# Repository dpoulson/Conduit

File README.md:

Conduit
=======

Conduit LARP equipment

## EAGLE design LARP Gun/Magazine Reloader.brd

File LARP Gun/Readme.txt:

Magazine uses ATTiny45

3 Analog inputs
2 PWM inputs

Program for Magazine:

Pin 0 - High if still ammo left
Pin 1 - Trigger (decrement ammo count by one)
Pin 2 - Add ammo (Admin only)
Pin 3 - Clear ammo (Admin only)

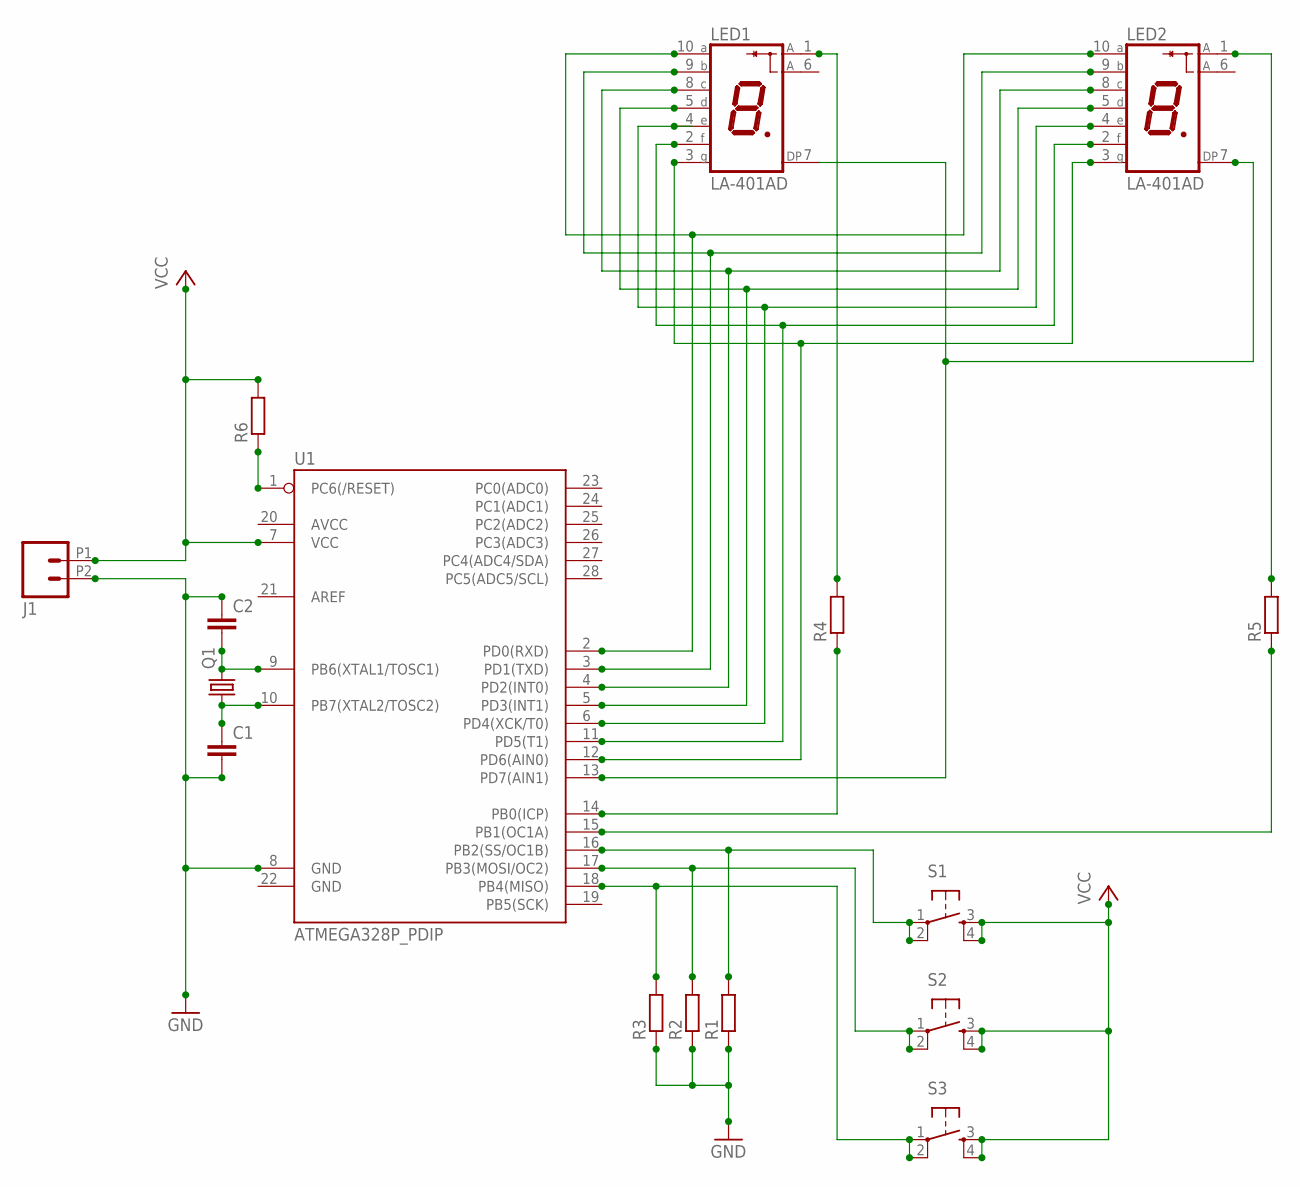
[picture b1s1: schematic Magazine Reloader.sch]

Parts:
C1, C2: C-EU025-025X050; C025-025X050
J1: M022.54MM_SCREWTERM; 1X02_2.54_SCREWTERM
LED1, LED2: LA-401AD; LA-401
Q1: CRYSTALHC49S; HC49/S
R1, R2, R3, R4, R5, R6: R-EU_0207/7; 0207/7
S1, S2, S3: TAC_SWITCHPTH; TACTILE-PTH
U1: ATMEGA328P_PDIP; DIL28-3

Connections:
GND: C1.2, C2.1, J1.P2 (2), R1.1, R2.1, R3.1, U1.8 (GND)
unnamed: LED1.3 (G), LED2.3 (G), U1.12 (PD6(AIN0))
unnamed: LED1.2 (F), LED2.2 (F), U1.11 (PD5(T1))
unnamed: LED1.4 (E), LED2.4 (E), U1.6 (PD4(XCK/T0))
unnamed: LED1.5 (D), LED2.5 (D), U1.5 (PD3(INT1))
unnamed: LED1.8 (C), LED2.8 (C), U1.4 (PD2(INT0))
unnamed: LED1.9 (B), LED2.9 (B), U1.3 (PD1(TXD))
unnamed: LED1.10 (A), LED2.10 (A), U1.2 (PD0(RXD))
unnamed: LED1.7 (DP), LED2.7 (DP), U1.13 (PD7(AIN1))
unnamed: R4.1, U1.14 (PB0(ICP))
unnamed: R5.1, U1.15 (PB1(OC1A))
unnamed: LED1.1 (A), R4.2
unnamed: LED2.1 (A), R5.2
unnamed: R3.2, S3.1, S3.2, U1.18 (PB4(MISO))
unnamed: R2.2, S2.1, S2.2, U1.17 (PB3(MOSI/OC2))
unnamed: R1.2, S1.1, S1.2, U1.16 (PB2(SS/OC1B))
unnamed: C2.2, Q1.2, U1.9 (PB6(XTAL1/TOSC1))
unnamed: C1.1, Q1.1, U1.10 (PB7(XTAL2/TOSC2))
unnamed: R6.1, U1.1 (PC6(/RESET))
VCC: J1.P1 (1), R6.2, S1.3, S1.4, S2.3, S2.4, S3.3, S3.4, U1.7 (VCC)

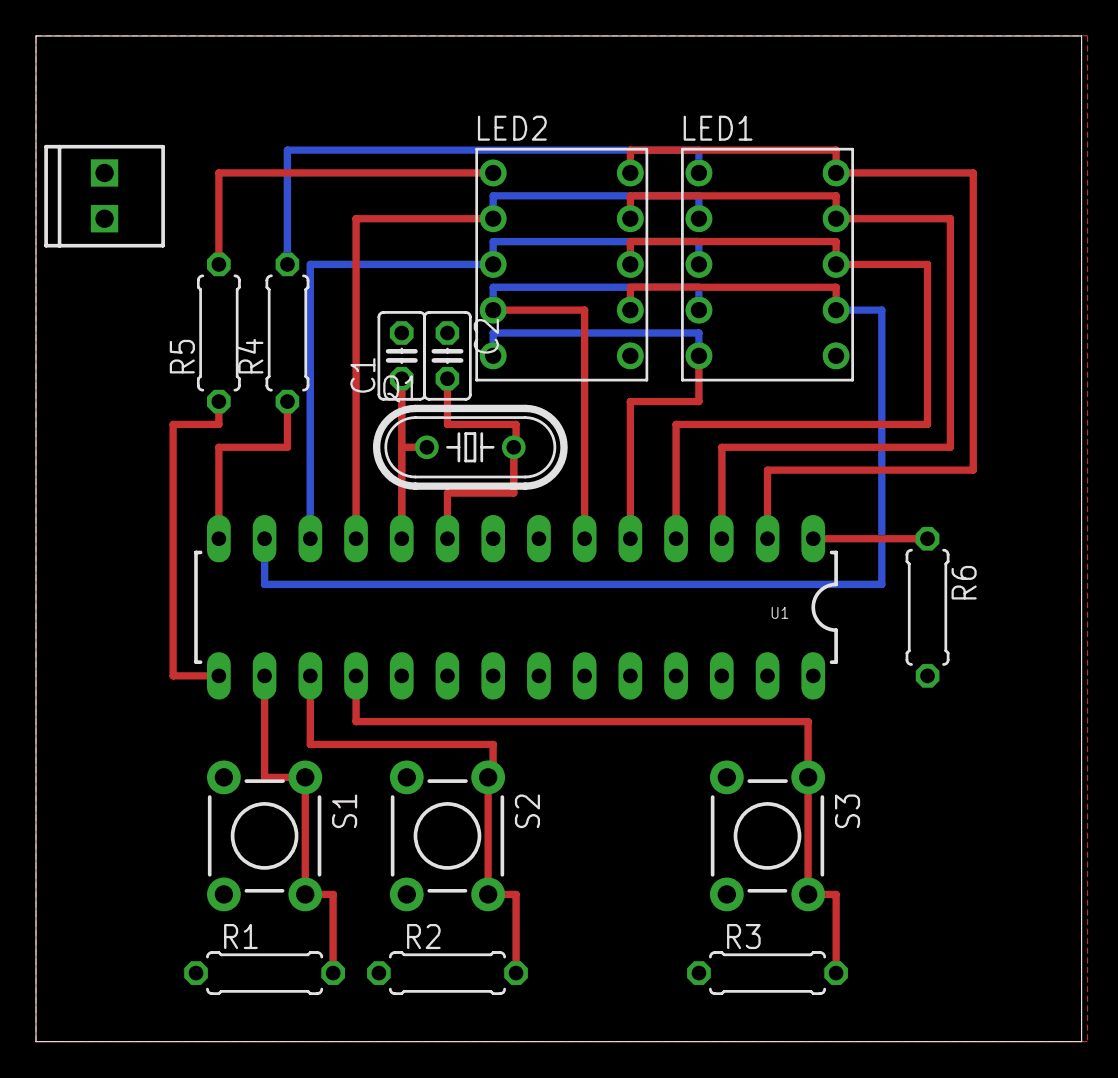
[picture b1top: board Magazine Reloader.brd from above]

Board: 2 copper layers, 58.1 x 55.9 mm, 16 parts (0 on the bottom side), 20 nets.

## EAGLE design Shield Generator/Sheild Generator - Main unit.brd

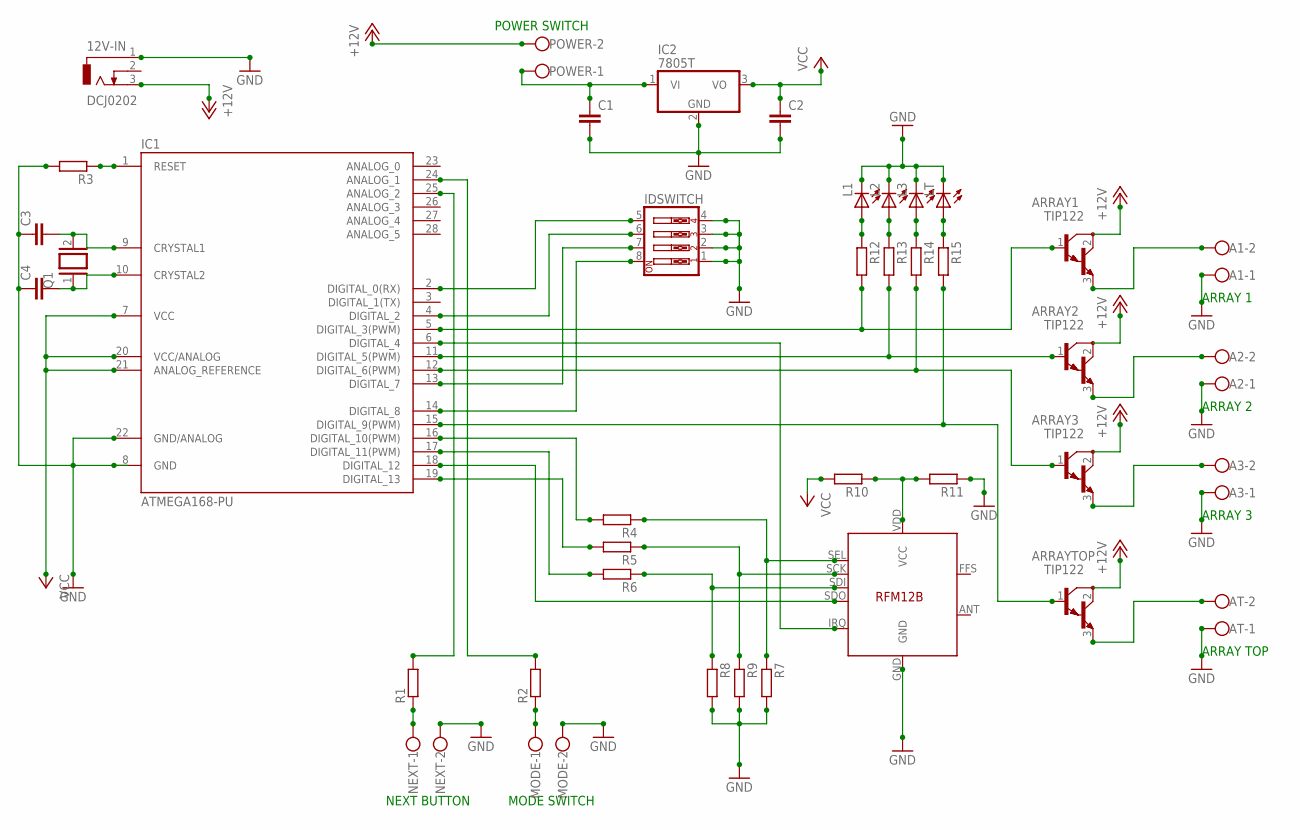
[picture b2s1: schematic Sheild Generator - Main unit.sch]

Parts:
12V-IN: DCJ0202
A1, A2, A3: W237-102
ARRAY1, ARRAY2, ARRAY3: TIP122; TO220
ARRAYTOP: TIP122; TO220
AT: W237-102
C1, C2, C3, C4: C-EU025-024X044; C025-024X044
IC1: ATMEGA168-PU; DIL28-3
IC2: 7805T; TO220H
IDSWITCH: SW_DIP-4; EDG-04
L1, L2, L3: LED3MM
LT: LED3MM
MODE: W237-102
NEXT: W237-102
POWER: W237-102
Q1: XTAL/S; QS
R1, R2, R3, R4, R5, R6, R7, R8, R9, R10, R11, R12, R13, R14, R15: R-EU_0204/7; 0204/7
U$1: RFM12B

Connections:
+5V: C2.1, IC1.7 (VCC), IC1.20 (VCC/ANALOG), IC1.21 (ANALOG_REFERENCE), IC2.3 (VO), R10.2
+12V: 12V-IN.3, ARRAY1.2 (C), ARRAY2.2 (C), ARRAY3.2 (C), ARRAYTOP.2 (C), POWER.2
GND: 12V-IN.1, A1.1, A2.1, A3.1, AT.1, C1.2, C2.2, C3.1, C4.1, IC1.8 (GND), IC1.22 (GND/ANALOG), IC2.2 (GND), IDSWITCH.1, IDSWITCH.2, IDSWITCH.3, IDSWITCH.4, L1.K (C), L2.K (C), L3.K (C), LT.K (C), MODE.2, NEXT.2, R3.2, R7.2, R8.2, R9.2, R11.1, U$1.GND
unnamed: ARRAY1.1 (B), IC1.5 (DIGITAL_3(PWM)), R12.2
unnamed: ARRAY2.1 (B), IC1.11 (DIGITAL_5(PWM)), R13.2
unnamed: ARRAY3.1 (B), IC1.12 (DIGITAL_6(PWM)), R14.2
unnamed: ARRAYTOP.1 (B), IC1.15 (DIGITAL_9(PWM)), R15.2
unnamed: IC1.2 (DIGITAL_0(RX)), IDSWITCH.5
unnamed: IC1.4 (DIGITAL_2), IDSWITCH.6
unnamed: IC1.13 (DIGITAL_7), IDSWITCH.7
unnamed: IC1.14 (DIGITAL_8), IDSWITCH.8
unnamed: NEXT.1, R1.1
unnamed: IC1.25 (ANALOG_2), R1.2
unnamed: A1.2, ARRAY1.3 (E)
unnamed: A2.2, ARRAY2.3 (E)
unnamed: A3.2, ARRAY3.3 (E)
unnamed: ARRAYTOP.3 (E), AT.2
unnamed: IC1.24 (ANALOG_1), R2.2
unnamed: MODE.1, R2.1
unnamed: C3.2, IC1.9 (CRYSTAL1), Q1.2
unnamed: C1.1, IC2.1 (VI), POWER.1
unnamed: C4.2, IC1.10 (CRYSTAL2), Q1.1
unnamed: R4.1, R7.1, U$1.SEL
unnamed: IC1.1 (RESET), R3.1
unnamed: R5.1, R9.1, U$1.SCK
unnamed: R6.1, R8.1, U$1.SDI
unnamed: IC1.6 (DIGITAL_4), U$1.IRQ
unnamed: IC1.16 (DIGITAL_10(PWM)), R4.2
unnamed: IC1.19 (DIGITAL_13), R5.2
unnamed: IC1.17 (DIGITAL_11(PWM)), R6.2
unnamed: IC1.18 (DIGITAL_12), U$1.SDO
unnamed: R10.1, R11.2, U$1.VDD (VCC)
unnamed: L1.A, R12.1
unnamed: L2.A, R13.1
unnamed: L3.A, R14.1
unnamed: LT.A, R15.1

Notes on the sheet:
POWER SWITCH
MODE SWITCH
NEXT BUTTON
ARRAY 1
ARRAY 2
ARRAY 3
ARRAY TOP

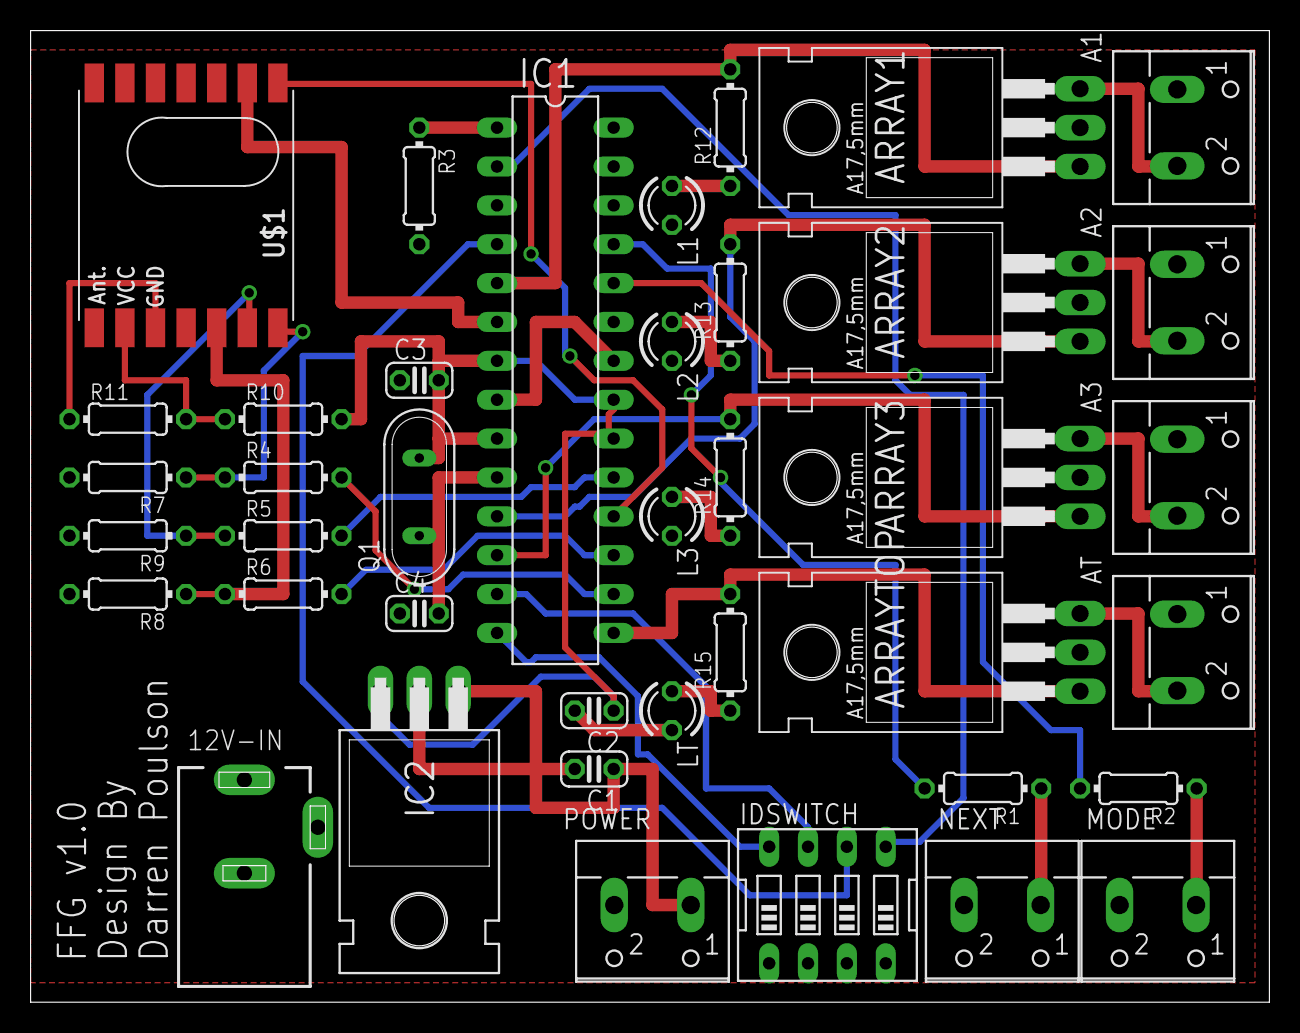
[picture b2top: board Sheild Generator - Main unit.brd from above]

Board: 2 copper layers, 81.0 x 63.5 mm, 40 parts (0 on the bottom side), 36 nets.

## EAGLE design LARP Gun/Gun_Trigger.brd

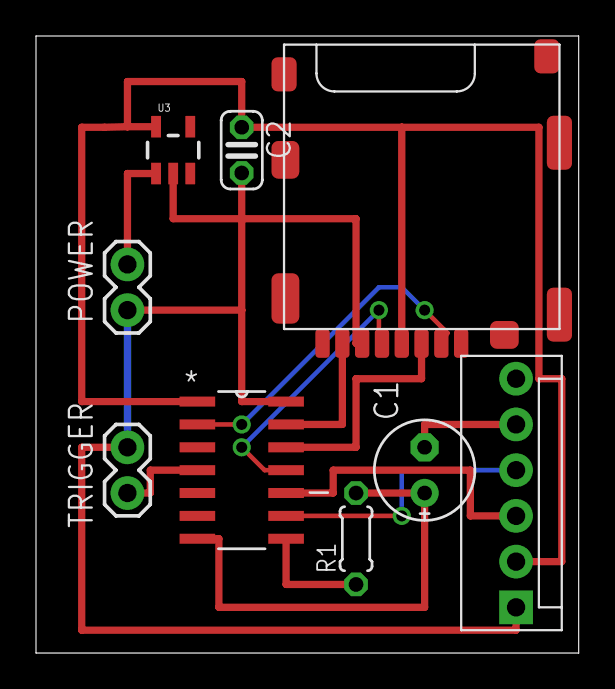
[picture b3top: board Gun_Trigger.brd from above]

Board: 2 copper layers, 30.2 x 34.3 mm, 9 parts (0 on the bottom side), 13 nets.

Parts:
AMMO: MOLEX-1X6
C1: E2,5-6E
C2: C025-024X044
MC: ATTINY84; SOIC127P600X175-14N
POWER: M02PTH; 1X02
R1: 0204/5
TRIGGER: M02PTH; 1X02
U3: SOT23-5
U$1: MICROSD_SPI_MODE; MICRO_SD_CONNECTOR

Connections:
3.3V: AMMO.2, C2.1, MC.1, U3.5, U$1.4
AMMO: AMMO.3, MC.10
GND: AMMO.1, C2.2, MC.14, POWER.2, TRIGGER.1, U3.2, U$1.6
unnamed: MC.4, TRIGGER.2
unnamed: MC.13, U$1.7
unnamed: MC.12, U$1.3
unnamed: MC.11, U$1.5
unnamed: MC.2, U$1.2
unnamed: MC.8, R1.1
unnamed: C1.+, MC.7, R1.2
SPEAKER: AMMO.5, C1.-
TRIGGER: AMMO.4, MC.9
VCC: POWER.1, U3.1

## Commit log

2014-03-15 Uploading work so far
2014-03-20 Tweaked board layout a little and shrunk by a few mm
2016-09-06 Updates to LARP gun. Circuit board for embedding in Magazine.
2016-09-08 Updated cad files, and working sketch for the magazine
2016-09-08 Added pull down resistors to the magazine board.
2016-09-08 First pass at magazine reloader.
2016-09-08 Added footprint for edge connector to magazine reloader

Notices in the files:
parts and their libraries:
SparkFun-PowerIC: Licensing: CC v3.0 Share-Alike You are welcome to use this library for commercial purposes.
SparkFun-Retired: Licensing:Creative Commons ShareAlike 4.0 International - https://creativecommons.org/licenses/by-sa/4.0
